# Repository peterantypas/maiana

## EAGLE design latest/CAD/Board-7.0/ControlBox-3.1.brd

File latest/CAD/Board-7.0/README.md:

# Board 7.0

This board is not yet completely validated, but its individual components are already proven.

Main improvements:

- The RX path features a MiniCircuits PSA4-5043+ LNA and a SAW filter from RFMI
- The DC/DC switch is now a synchronous buck with spread spectrum support for reduced EMI
- The 10000uF supercapacitor is back as an option in case transmission currents cause too much voltage drop at the input
- There are explicit signals to control status LEDs (GNSS, RX, TX)

There are two assembly variants, with and without the supercap. Firmware will support either without any special considerations, as it enforces a 5 second minimum interval between consecutive transmissions. This is more than enough to recharge a depleted supercap.

The control circuit is designed to fit inside a Hammond 1551KFLGY case (with appropriate cutouts). It features a single on/off button as well as a "TX on/off" slider switch. Control logic is implemented in a customized GreenPAK mixed signal IC (SLG46537V):

Using this type of IC avoids yet another microcontroller with firmware. The GreenPAK instruments latched overcurrent protection, debounces the on/off button, and acts as an LED driver. The design file for the IC (.gp5) is included. If you are an electronics enthusiast and you're not familiar with this family of ICs yet, I think it's time to change that ;)

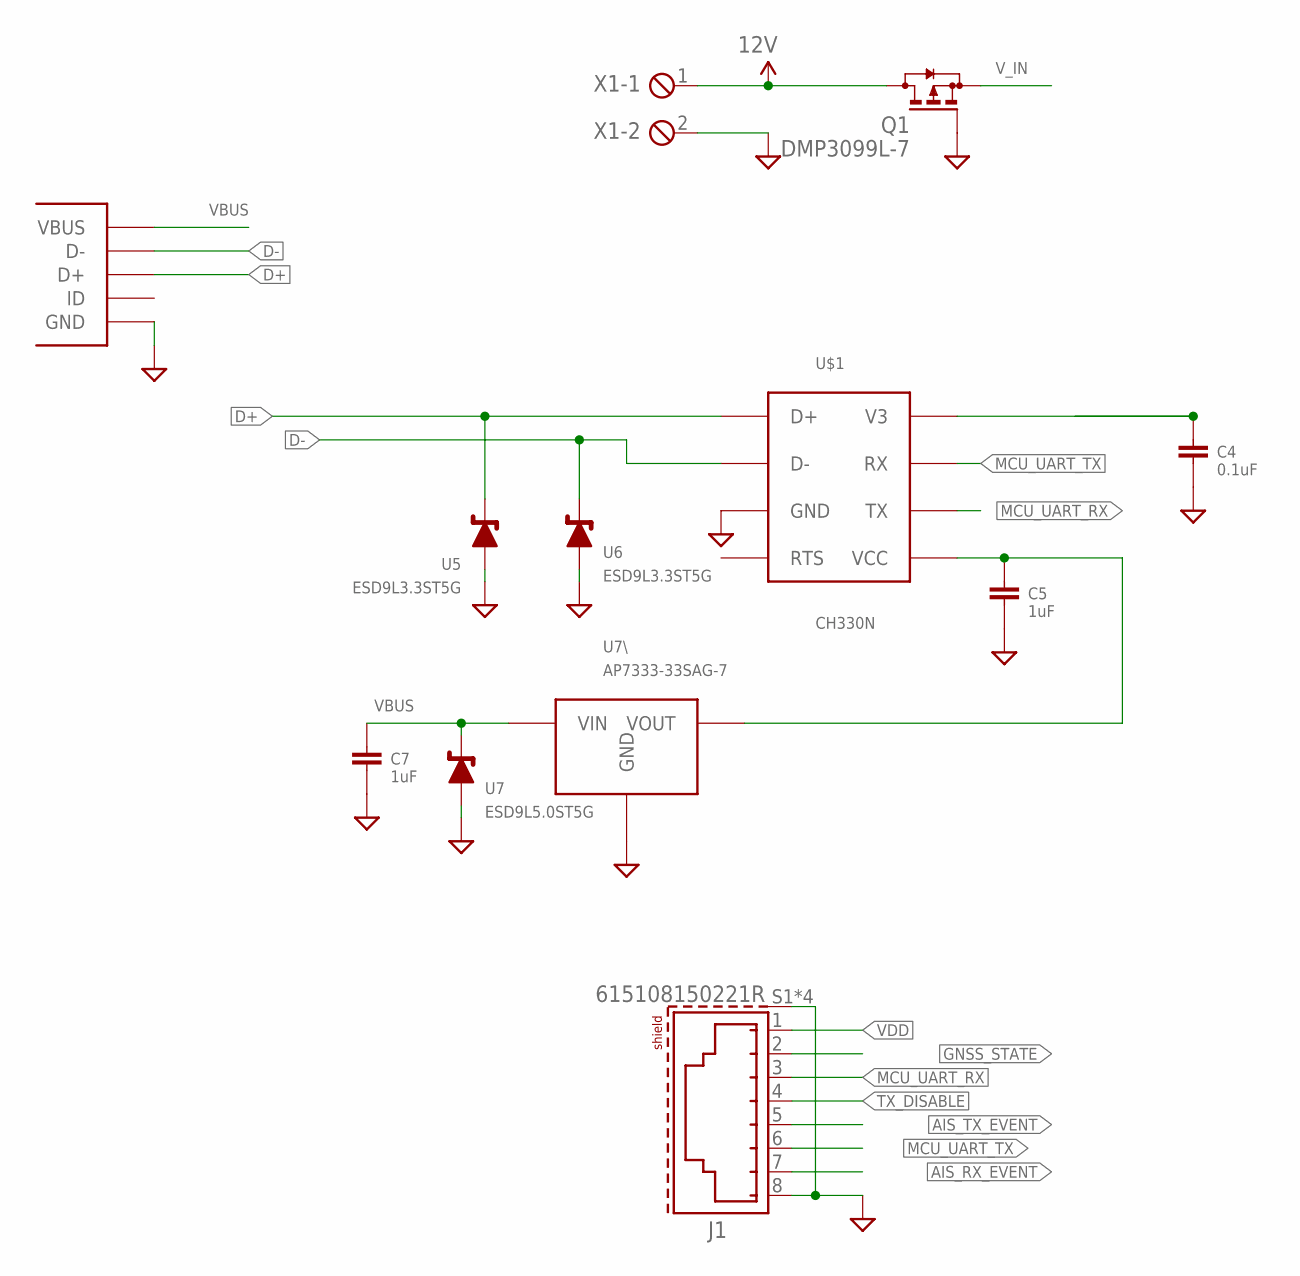
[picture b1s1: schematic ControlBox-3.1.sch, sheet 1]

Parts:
C4: 0.1uF; 0603
C5, C7: 1uF; 0603
J1: 615108150221R
Q1: DMP3099L-7; SOT23
U5, U6: ESD9L3.3ST5G; SODFL1006X40N
U7: ESD9L5.0ST5G; SODFL1006X40N
U7\: AP7333-33SAG-7; SOT-23
U$1: CH330N; SOIC-8
U$2: MICRO_USB
X1: MPT2; 2POL254

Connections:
12V: Q1.3 (D), X1.1
AIS_RX_EVENT: J1.7; also elsewhere on the board
AIS_TX_EVENT: J1.5; also elsewhere on the board
D+: U5.1, U$1.1 (D+), U$2.D+
D-: U6.1, U$1.2 (D-), U$2.D-
GND: C4.P$2 (2), C5.P$2 (2), C7.P$2 (2), J1.8, J1.S1 (SHIELD), J1.S2 (SHIELD), J1.S3 (SHIELD), J1.S4 (SHIELD), Q1.1 (G), U5.2, U6.2, U7.2, U7\.3 (GND), U$1.3 (GND), U$2.GND, U$2.MT1 (GND), U$2.MT2 (GND), U$2.P$1 (GND), U$2.P$2 (GND), X1.2; also elsewhere on the board
GNSS_STATE: J1.2; also elsewhere on the board
MCU_UART_RX: J1.3, U$1.6 (TX)
MCU_UART_TX: J1.6, U$1.7 (RX)
unnamed: C4.P$1 (1), U$1.8 (V3)
unnamed: C5.P$1 (1), U7\.2 (VOUT), U$1.5 (VCC)
TX_DISABLE: J1.4; also elsewhere on the board
VBUS: C7.P$1 (1), U7.1, U7\.1 (VIN), U$2.VBUS
VDD: J1.1; also elsewhere on the board
V_IN: Q1.2 (S); also elsewhere on the board

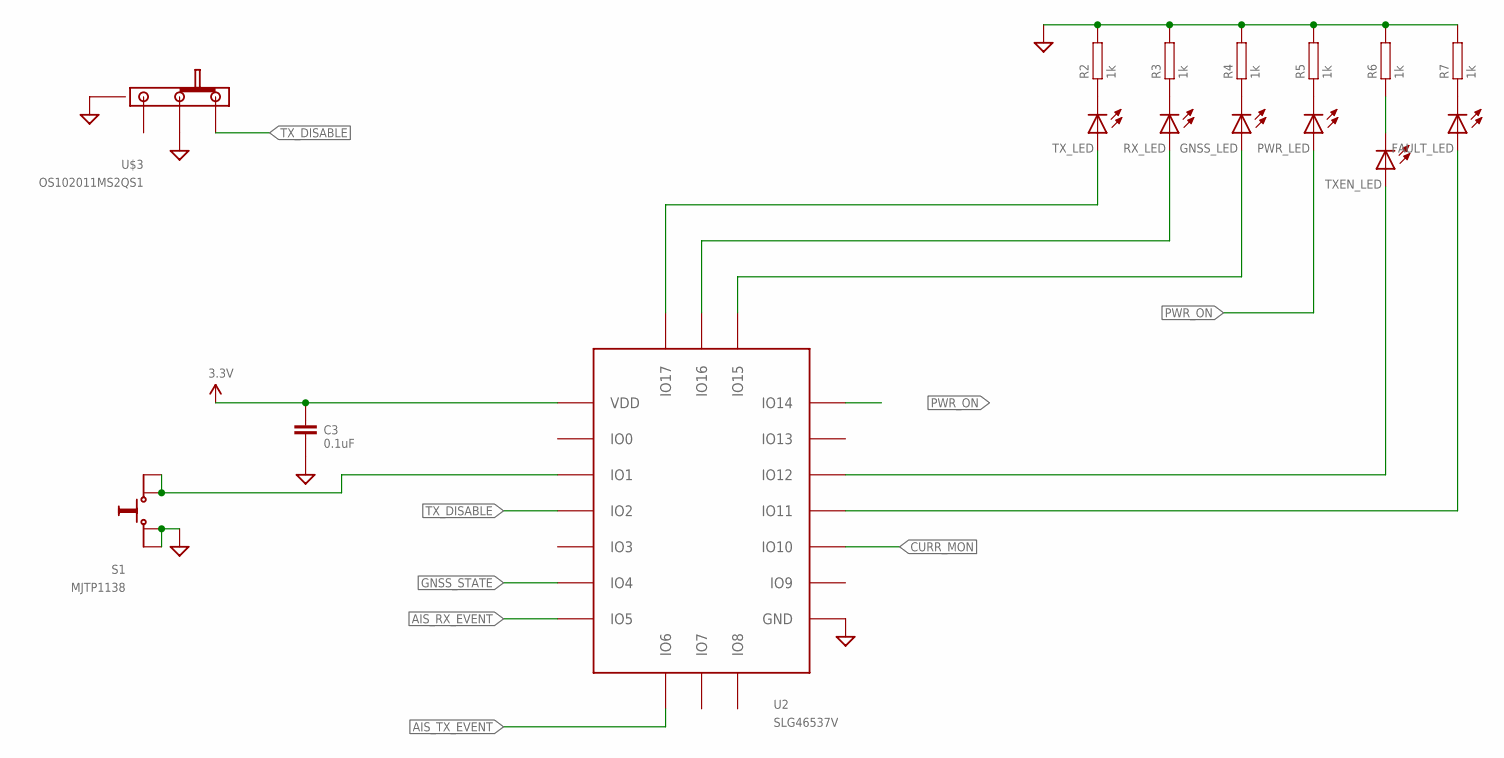
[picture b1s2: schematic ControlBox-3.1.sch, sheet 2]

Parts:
C3: 0.1uF; 0603
FAULT_LED: LEDCHIPLED_0603; CHIPLED_0603
GNSS_LED: LEDCHIPLED_0603; CHIPLED_0603
PWR_LED: LEDCHIPLED_0603; CHIPLED_0603
R2, R3, R4, R5, R6, R7: 1k; 0603
RX_LED: LEDCHIPLED_0603; CHIPLED_0603
S1: MJTP1138
TXEN_LED: LEDCHIPLED_0603; CHIPLED_0603
TX_LED: LEDCHIPLED_0603; CHIPLED_0603
U2: SLG46537V; STQFN20L
U$3: OS102011MS2QS1; SPDT-PTH

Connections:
3.3V: C3.P$1 (1), U2.P$1 (VDD); also elsewhere on the board
AIS_RX_EVENT: U2.P$7 (IO5); also elsewhere on the board
AIS_TX_EVENT: U2.P$8 (IO6); also elsewhere on the board
BTN: S1.P$1 (A), S1.P$4 (A), U2.P$3 (IO1)
CURR_MON: U2.P$13 (IO10); also elsewhere on the board
FAULT_LED: FAULT_LED.A, U2.P$14 (IO11)
GND: C3.P$2 (2), R2.P$2, R3.P$2, R4.P$2, R5.P$2, R6.P$2, R7.P$2, S1.P$2 (B), S1.P$3 (B), U2.P$11 (GND), U$3.P$2 (2), U$3.P$4 (SHLD), U$3.P$5 (SHLD); also elsewhere on the board
GNSS_LED: GNSS_LED.A, U2.P$18 (IO15)
GNSS_STATE: U2.P$6 (IO4); also elsewhere on the board
unnamed: R2.P$1, TX_LED.C
unnamed: R3.P$1, RX_LED.C
unnamed: GNSS_LED.C, R4.P$1
unnamed: PWR_LED.C, R5.P$1
unnamed: R6.P$1, TXEN_LED.C
unnamed: FAULT_LED.C, R7.P$1
PWR_ON: PWR_LED.A, U2.P$17 (IO14); also elsewhere on the board
RX_LED: RX_LED.A, U2.P$19 (IO16)
TX_DISABLE: U2.P$4 (IO2), U$3.P$1 (1); also elsewhere on the board
TX_EN_LED: TXEN_LED.A, U2.P$15 (IO12)
TX_LED: TX_LED.A, U2.P$20 (IO17)

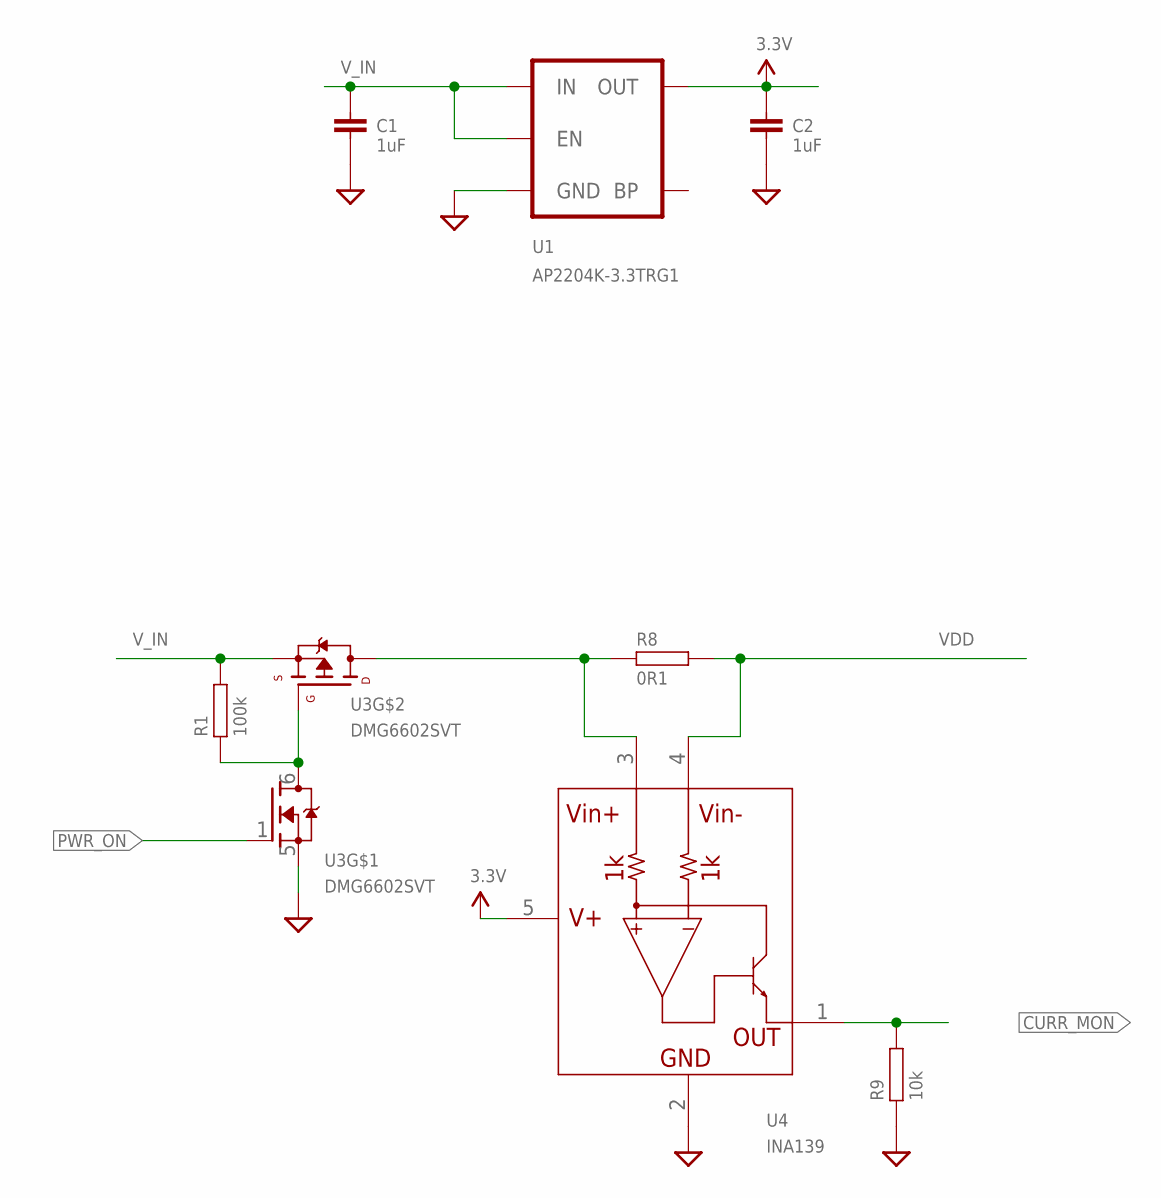
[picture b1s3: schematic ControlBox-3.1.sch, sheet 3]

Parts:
C1, C2: 1uF; 0603
R1: 100k; 0603
R8: 0R1; 1206
R9: 10k; 0603
U1: AP2204K-3.3TRG1; SOT23-5
U3: DMG6602SVT; SOT23-6
U4: INA139; SOT23-5

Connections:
3.3V: C2.P$1 (1), U1.5 (OUT), U4.5 (V+); also elsewhere on the board
CURR_MON: R9.P$2, U4.1 (OUT); also elsewhere on the board
GND: C1.P$2 (2), C2.P$2 (2), R9.P$1, U1.2 (GND), U3.5 (S), U4.2 (GND); also elsewhere on the board
unnamed: R1.P$1, U3.3 (G), U3.6 (D)
unnamed: R8.P$1, U3.4 (D), U4.3 (VIN+)
PWR_ON: U3.1 (G); also elsewhere on the board
VDD: R8.P$2, U4.4 (VIN-); also elsewhere on the board
V_IN: C1.P$1 (1), R1.P$2, U1.1 (IN), U1.3 (EN), U3.2 (S); also elsewhere on the board

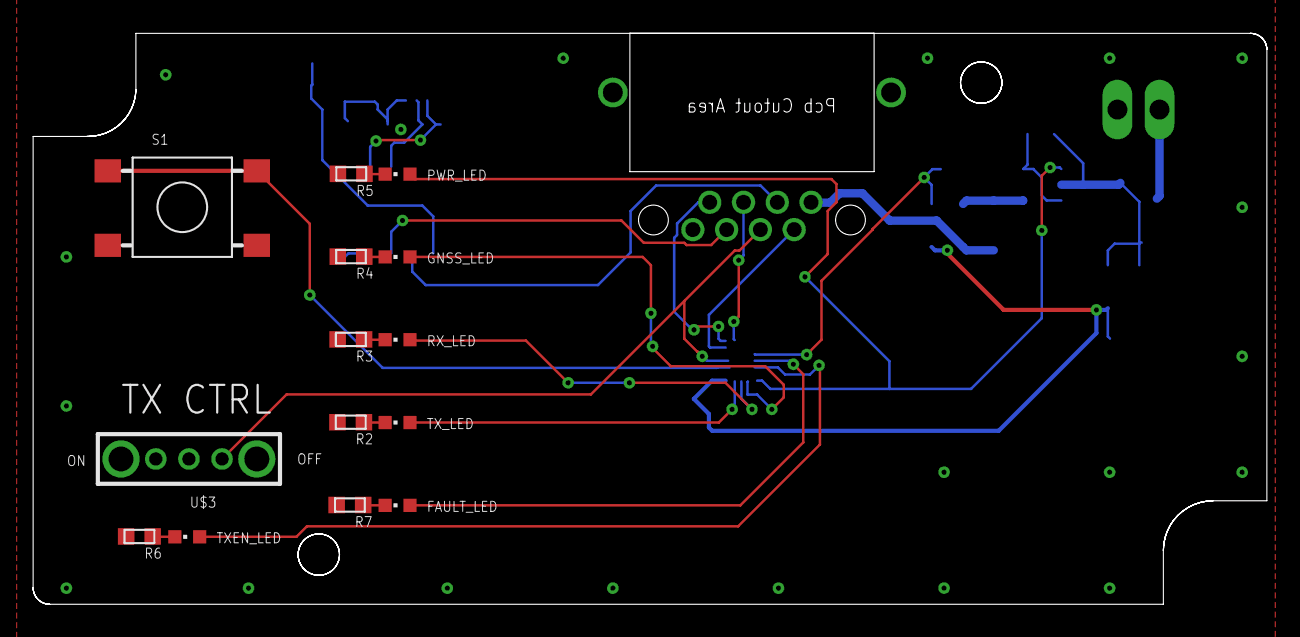
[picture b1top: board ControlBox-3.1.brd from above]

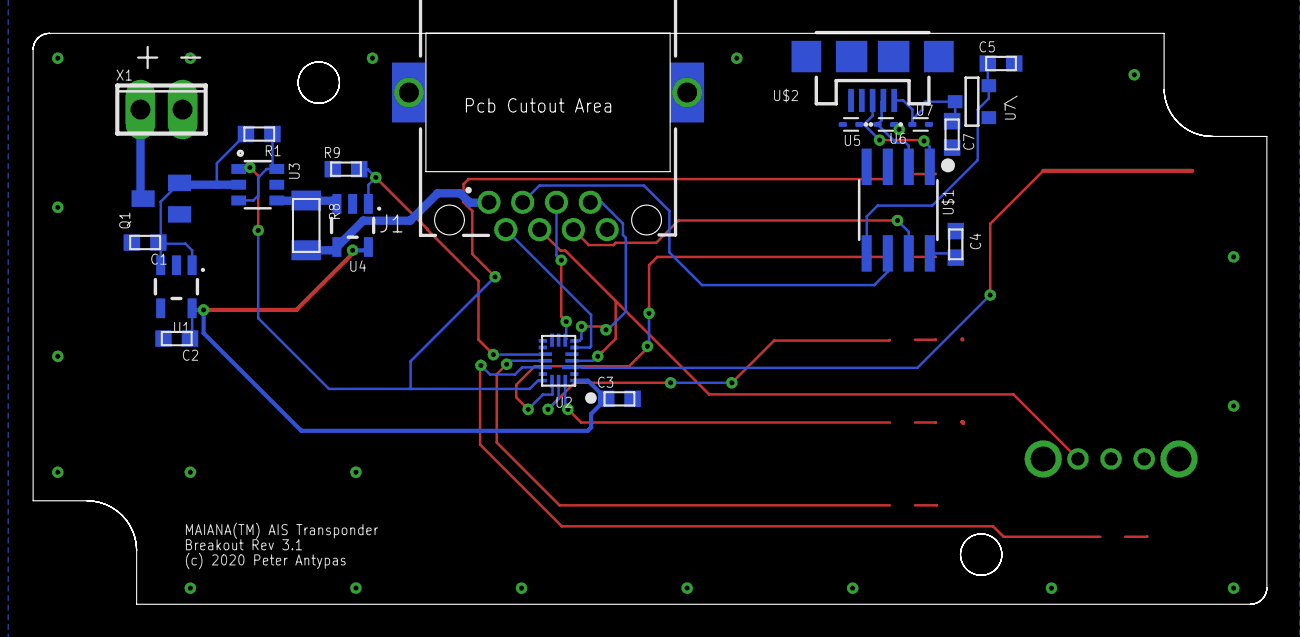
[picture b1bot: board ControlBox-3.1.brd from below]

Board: 2 copper layers, 74.5 x 34.5 mm, 36 parts (22 on the bottom side), 32 nets.

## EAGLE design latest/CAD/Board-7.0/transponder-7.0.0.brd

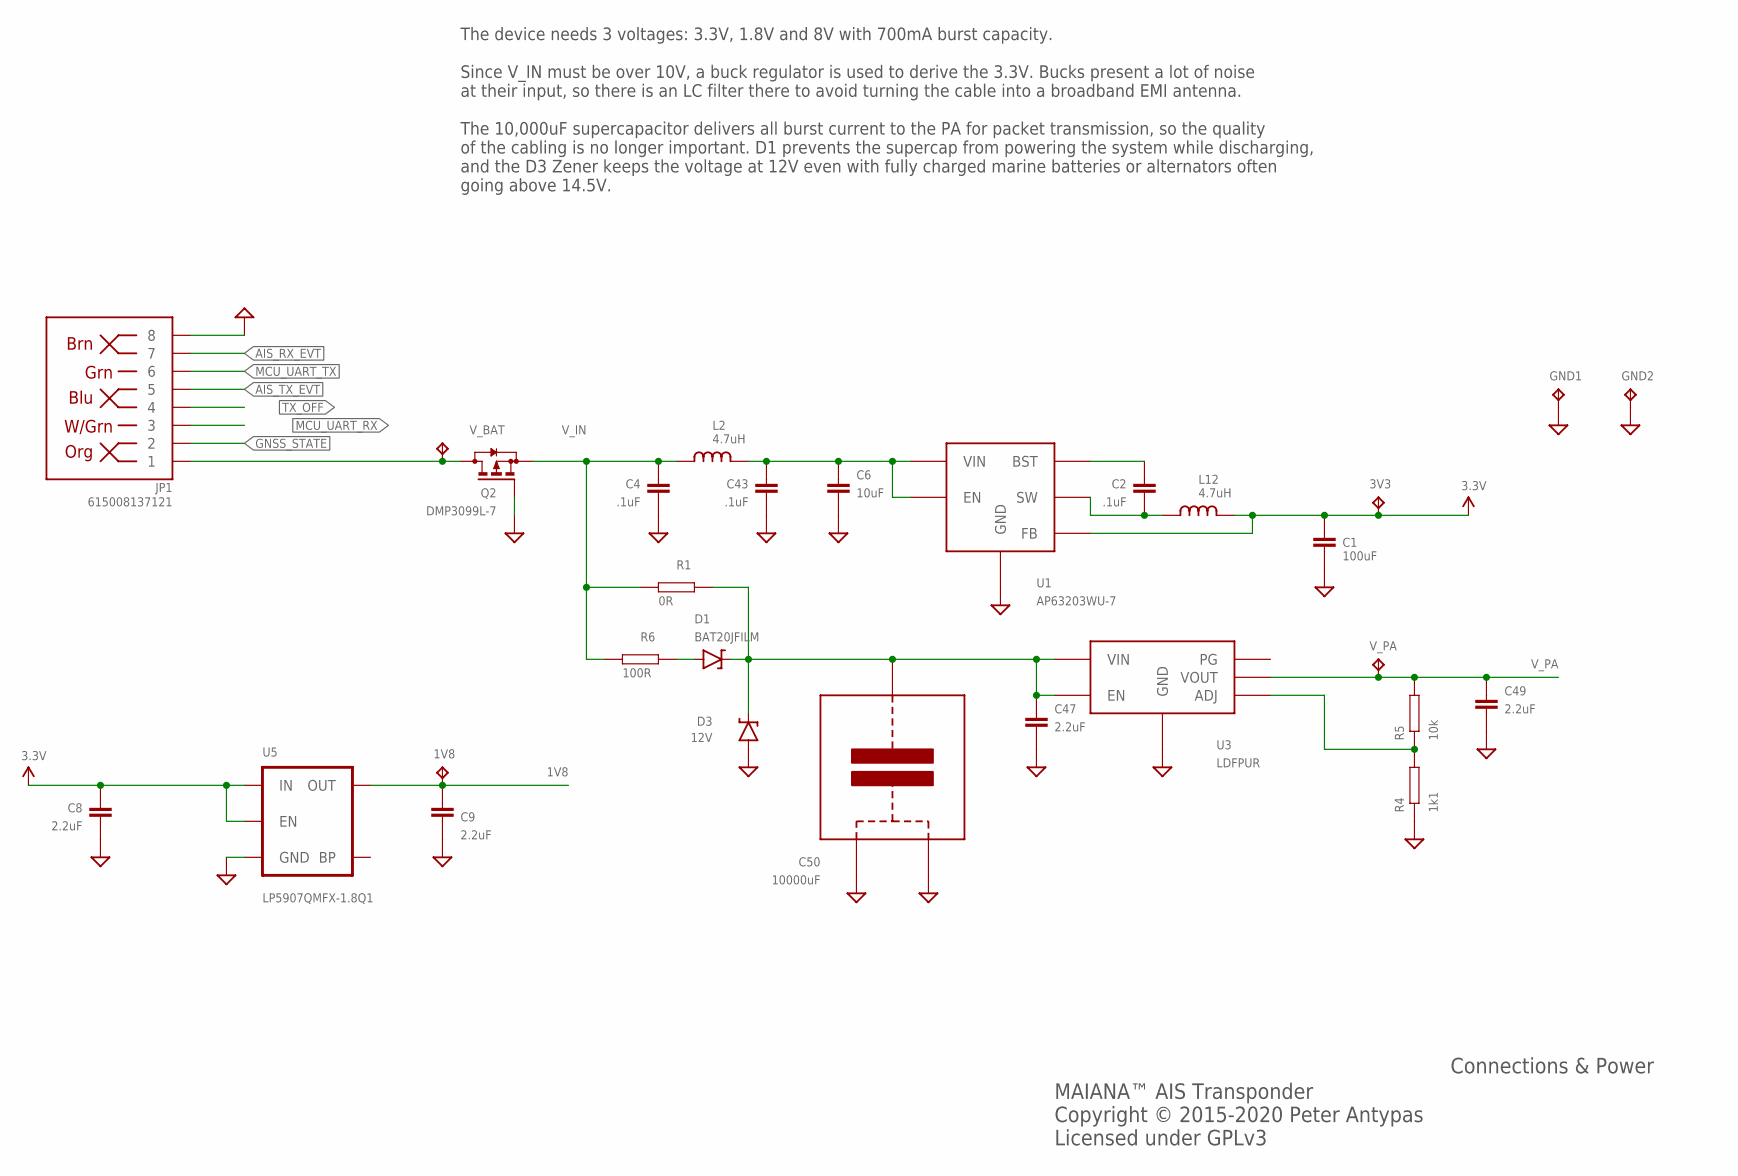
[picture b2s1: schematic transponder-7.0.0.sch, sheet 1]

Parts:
1V8, 3V3: TPTP12R; TP12R
C1: 100uF; 1206; PARTNO JMK316ABJ107ML-T
C2, C4, C43: .1uF; 0603; PARTNO EMK107B7104KAHT
C6: 10uF; 0805; PARTNO EMK212ABJ106KG-T
C8, C9, C47, C49: 2.2uF; 0603; PARTNO EMK107BJ225KA-T
C50: 10000uF; BZ05; PARTNO BZ05CA103ZSB
D1: BAT20JFILM; SOD323; PARTNO BAT20JFILM
D3: 12V; SOD-323; PARTNO MM3Z12VST1G
GND1, GND2: TPTP16R; TP16R
JP1: 615008137121; RJ45-8; PARTNO ‎615008137121‎
L2, L12: 4.7uH; 0805; PARTNO MLZ2012M4R7WT000
Q2: DMP3099L-7; SOT23; PARTNO DMP3099L-7
R1: 0R; 0603; PARTNO RC0603FR-070RL
R4: 1k1; 0603; PARTNO RC0603JR-071K1L
R5: 10k; 0603; PARTNO RC0603JR-0710KL
R6: 100R; 0603; PARTNO RC0603FR-07100RL
U1: AP63203WU-7; SOT23-6
U3: LDFPUR; DFN-6; PARTNO LDFPUR
U5: LP5907QMFX-1.8Q1; SOT23-5; PARTNO LP5907QMFX-1.8Q1
V_BAT: TPTP12R; TP12R
V_PA: TPTP12R; TP12R

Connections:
1V8: 1V8.TP, C9.P$1 (1), U5.5 (OUT); also elsewhere on the board
3.3V: 3V3.TP, C1.P$1 (1), C8.P$1 (1), L12.P$2 (2), U1.1 (FB), U5.1 (IN), U5.3 (EN); also elsewhere on the board
AIS_RX_EVT: JP1.7; also elsewhere on the board
AIS_TX_EVT: JP1.5; also elsewhere on the board
BST: C2.P$1 (1), U1.6 (BST)
GND: C1.P$2 (2), C4.P$2 (2), C6.P$2 (2), C8.P$2 (2), C9.P$2 (2), C43.P$2 (2), C47.P$2 (2), C49.P$2 (2), C50.P$1, C50.P$2, D3.A, GND1.TP, GND2.TP, JP1.8, Q2.1 (G), R4.P$1, U1.4 (GND), U3.P$4 (GND), U3.P$7 (GND), U5.2 (GND); also elsewhere on the board
GNSS_STATE: JP1.2; also elsewhere on the board
MCU_UART_RX: JP1.3; also elsewhere on the board
MCU_UART_TX: JP1.6; also elsewhere on the board
unnamed: D1.A, R6.P$2
unnamed: C6.P$1 (1), C43.P$1 (1), L2.P$2 (2), U1.2 (EN), U1.3 (VIN)
unnamed: R4.P$2, R5.P$1, U3.P$2 (ADJ)
SW: C2.P$2 (2), L12.P$1 (1), U1.5 (SW)
TX_OFF: JP1.4; also elsewhere on the board
V_BAT: JP1.1, Q2.3 (D), V_BAT.TP
V_IN: C4.P$1 (1), L2.P$1 (1), Q2.2 (S), R1.P$1, R6.P$1
V_PA: C49.P$1 (1), R5.P$2, U3.P$1 (VOUT), V_PA.TP; also elsewhere on the board
V_PA_SRC: C47.P$1 (1), C50.P$3, D1.C, D3.C, R1.P$2, U3.P$5 (EN), U3.P$6 (VIN)

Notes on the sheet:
Connections & Power
MAIANA™ AIS Transponder Copyright © 2015-2020 Peter Antypas Licensed under GPLv3
The device needs 3 voltages: 3.3V, 1.8V and 8V with 700mA burst capacity. Since V_IN must be over 10V, a buck regulator is used to derive the 3.3V. Bucks present a lot of noise at their input, so there is an LC filter there to avoid turning the cable into a broadband EMI antenna. The 10,000uF super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

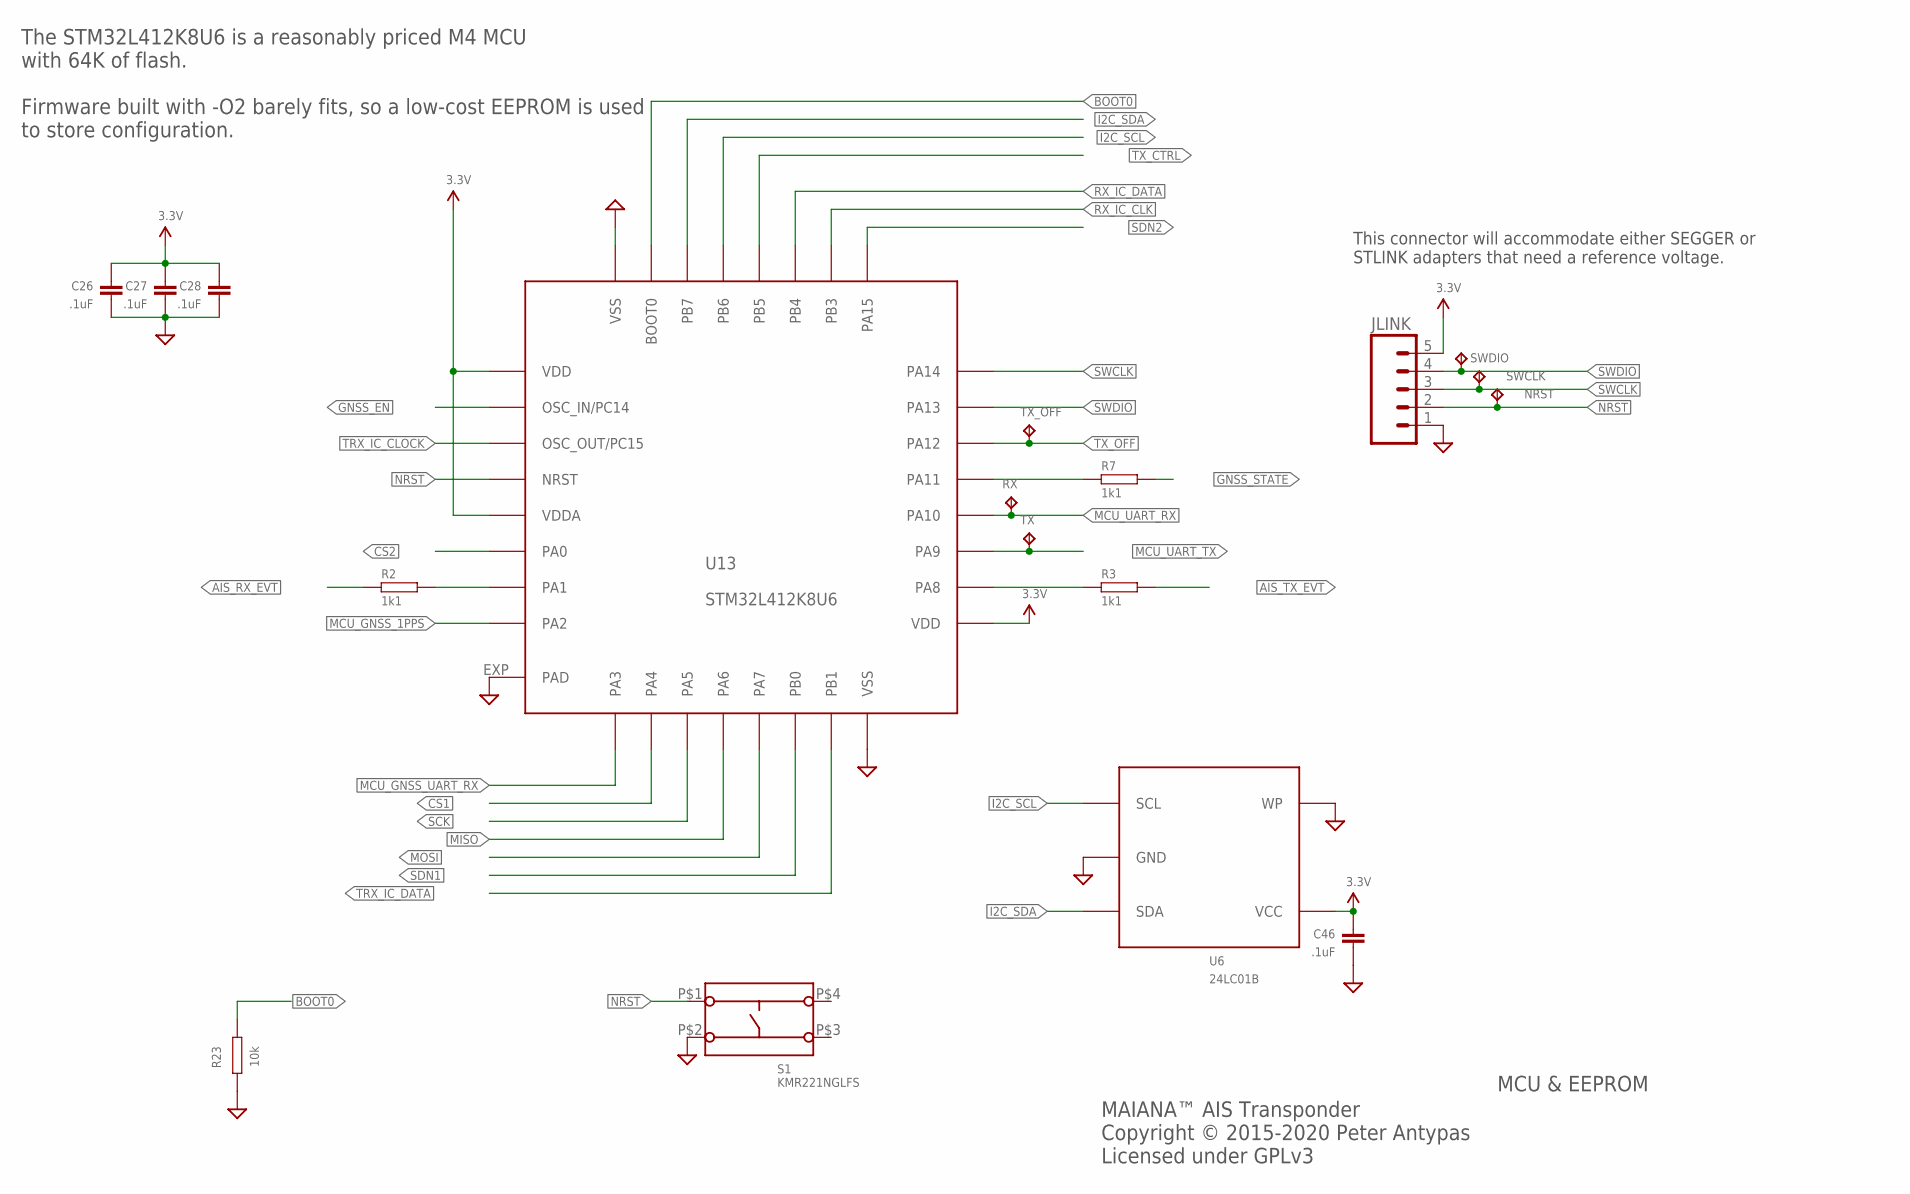
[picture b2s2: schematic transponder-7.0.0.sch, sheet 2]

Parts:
C26, C27, C28, C46: .1uF; 0603; PARTNO EMK107B7104KAHT
JLINK: M05PTH; 1X05
NRST: TPTP12R; TP12R
R2, R3, R7: 1k1; 0603; PARTNO RC0603JR-071K1L
R23: 10k; 0603; PARTNO RC0603JR-0710KL
RX: TPTP12R; TP12R
S1: KMR221NGLFS
SWCLK: TPTP12R; TP12R
SWDIO: TPTP12R; TP12R
TX: TPTP12R; TP12R
TX_OFF: TPTP12R; TP12R
U6: 24LC01B; SOT23-5; PARTNO 24LC01BT-I/OT
U13: STM32L412K8U6; QFN32; PARTNO STM32L412K8U6

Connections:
3.3V: C26.P$1 (1), C27.P$1 (1), C28.P$1 (1), C46.P$1 (1), JLINK.5, U6.4 (VCC), U13.1 (VDD), U13.5 (VDDA), U13.17 (VDD); also elsewhere on the board
AIS_RX_EVT: R2.P$1; also elsewhere on the board
AIS_TX_EVT: R3.P$2; also elsewhere on the board
BOOT0: R23.P$1, U13.31 (BOOT0)
CS1: U13.10 (PA4); also elsewhere on the board
CS2: U13.6 (PA0); also elsewhere on the board
GND: C26.P$2 (2), C27.P$2 (2), C28.P$2 (2), C46.P$2 (2), JLINK.1, R23.P$2, S1.P$2 (S2), U6.2 (GND), U6.5 (WP), U13.16 (VSS), U13.32 (VSS), U13.EXP (PAD); also elsewhere on the board
GNSS_EN: U13.2 (OSC_IN/PC14); also elsewhere on the board
GNSS_STATE: R7.P$2; also elsewhere on the board
I2C_SCL: U6.1 (SCL), U13.29 (PB6)
I2C_SDA: U6.3 (SDA), U13.30 (PB7)
MCU_GNSS_1PPS: U13.8 (PA2); also elsewhere on the board
MCU_GNSS_UART_RX: U13.9 (PA3); also elsewhere on the board
MCU_UART_RX: RX.TP, U13.20 (PA10); also elsewhere on the board
MCU_UART_TX: TX.TP, U13.19 (PA9); also elsewhere on the board
MISO: U13.12 (PA6); also elsewhere on the board
MOSI: U13.13 (PA7); also elsewhere on the board
unnamed: R2.P$2, U13.7 (PA1)
unnamed: R3.P$1, U13.18 (PA8)
unnamed: R7.P$1, U13.21 (PA11)
NRST: JLINK.2, NRST.TP, S1.P$1 (S1), U13.4 (NRST)
RX_IC_CLK: U13.26 (PB3); also elsewhere on the board
RX_IC_DATA: U13.27 (PB4); also elsewhere on the board
SCK: U13.11 (PA5); also elsewhere on the board
SDN1: U13.14 (PB0); also elsewhere on the board
SDN2: U13.25 (PA15); also elsewhere on the board
SWCLK: JLINK.3, SWCLK.TP, U13.24 (PA14)
SWDIO: JLINK.4, SWDIO.TP, U13.23 (PA13)
TRX_IC_CLOCK: U13.3 (OSC_OUT/PC15); also elsewhere on the board
TRX_IC_DATA: U13.15 (PB1); also elsewhere on the board
TX_CTRL: U13.28 (PB5); also elsewhere on the board
TX_OFF: TX_OFF.TP, U13.22 (PA12); also elsewhere on the board

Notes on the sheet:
MCU & EEPROM
MAIANA™ AIS Transponder Copyright © 2015-2020 Peter Antypas Licensed under GPLv3
The STM32L412K8U6 is a reasonably priced M4 MCU with 64K of flash. Firmware built with -O2 barely fits, so a low-cost EEPROM is used to store configuration.
This connector will accommodate either SEGGER or STLINK adapters that need a reference voltage.

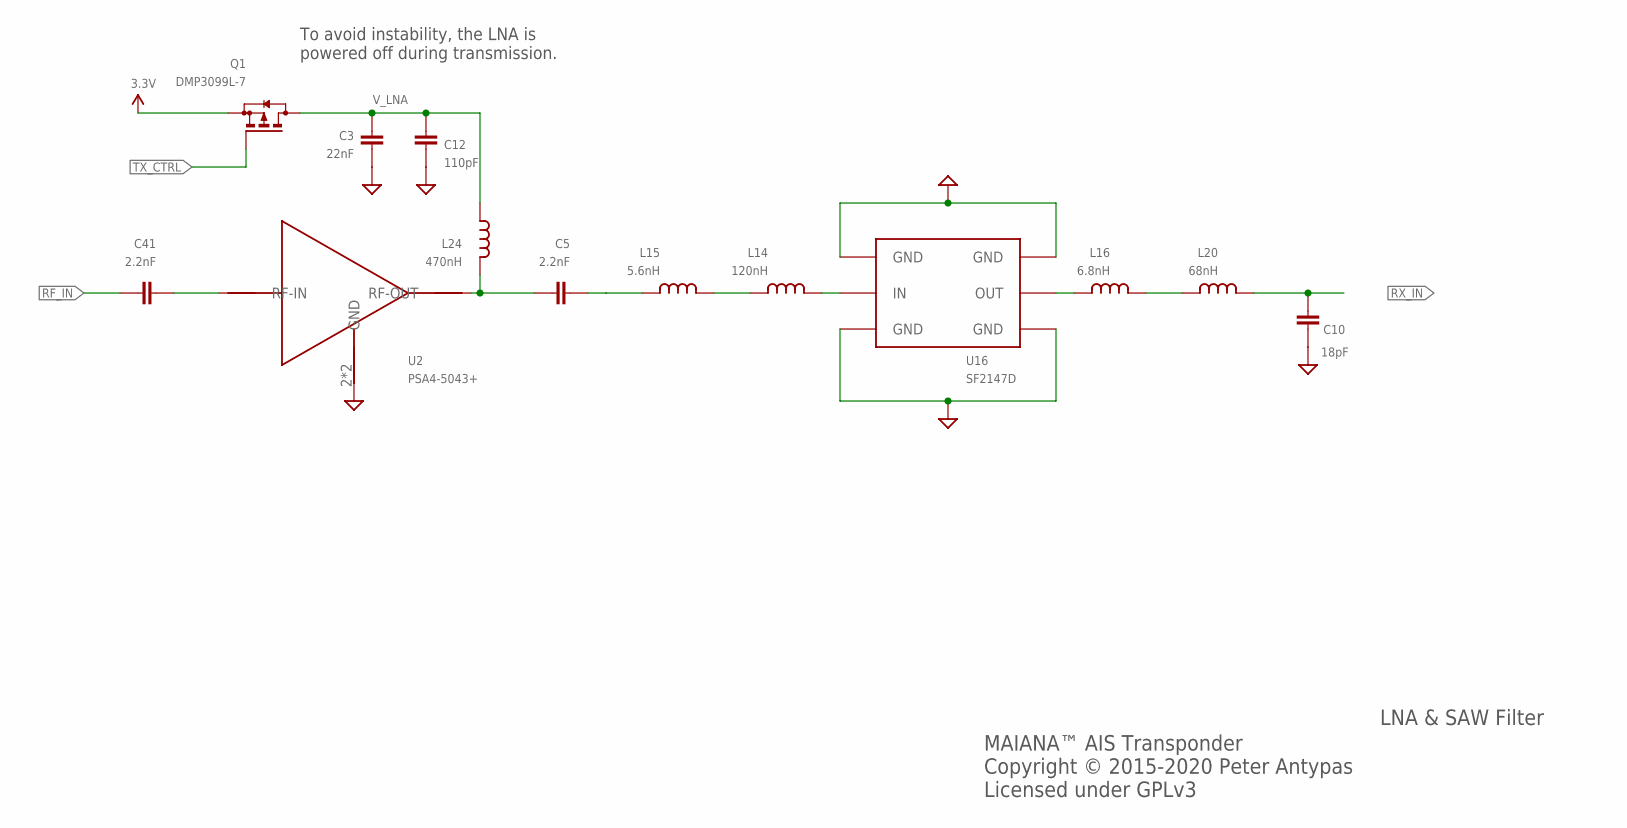
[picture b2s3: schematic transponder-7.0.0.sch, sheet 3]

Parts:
C3: 22nF; 0603; PARTNO GRM188R71E223KA01D
C5, C41: 2.2nF; 0603; PARTNO GRM1885C1H222JA01J
C10: 18pF; 0603; PARTNO 06035A180JAT4A
C12: 110pF; 0603; PARTNO GRM1885C2A111JA01D
L14: 120nH; 0603; PARTNO LQW18ASR12G0ZD
L15: 5.6nH; 0603; PARTNO LQW18AN5N6G8ZD
L16: 6.8nH; 0603; PARTNO LQW18AN6N8C10D
L20: 68nH; 0603; PARTNO LQW18AN68NG00D
L24: 470nH; 0603; PARTNO HK1608R47J-T
Q1: DMP3099L-7; SOT23; PARTNO DMP3099L-7
U2: PSA4-5043+
U16: SF2147D; SAW_FILTER1; PARTNO SF2147D

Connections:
3.3V: Q1.2 (S); also elsewhere on the board
GND: C3.P$2 (2), C10.P$1 (1), C12.P$1 (1), U2.2 (GND), U2.4 (GND), U16.P$1 (GND), U16.P$3 (GND), U16.P$4 (GND), U16.P$6 (GND); also elsewhere on the board
unnamed: L14.P$1 (1), U16.P$2 (IN)
unnamed: C41.P$2 (2), U2.3 (RF-IN)
unnamed: L14.P$2 (2), L15.P$1 (1)
unnamed: C5.P$1 (1), L24.P$2 (2), U2.1 (RF-OUT)
unnamed: C5.P$2 (2), L15.P$2 (2)
unnamed: L16.P$2 (2), U16.P$5 (OUT)
unnamed: L16.P$1 (1), L20.P$2 (2)
RF_IN: C41.P$1 (1); also elsewhere on the board
RX_IN: C10.P$2 (2), L20.P$1 (1); also elsewhere on the board
TX_CTRL: Q1.1 (G); also elsewhere on the board
V_LNA: C3.P$1 (1), C12.P$2 (2), L24.P$1 (1), Q1.3 (D)

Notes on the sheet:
LNA & SAW Filter
MAIANA™ AIS Transponder Copyright © 2015-2020 Peter Antypas Licensed under GPLv3
To avoid instability, the LNA is powered off during transmission.

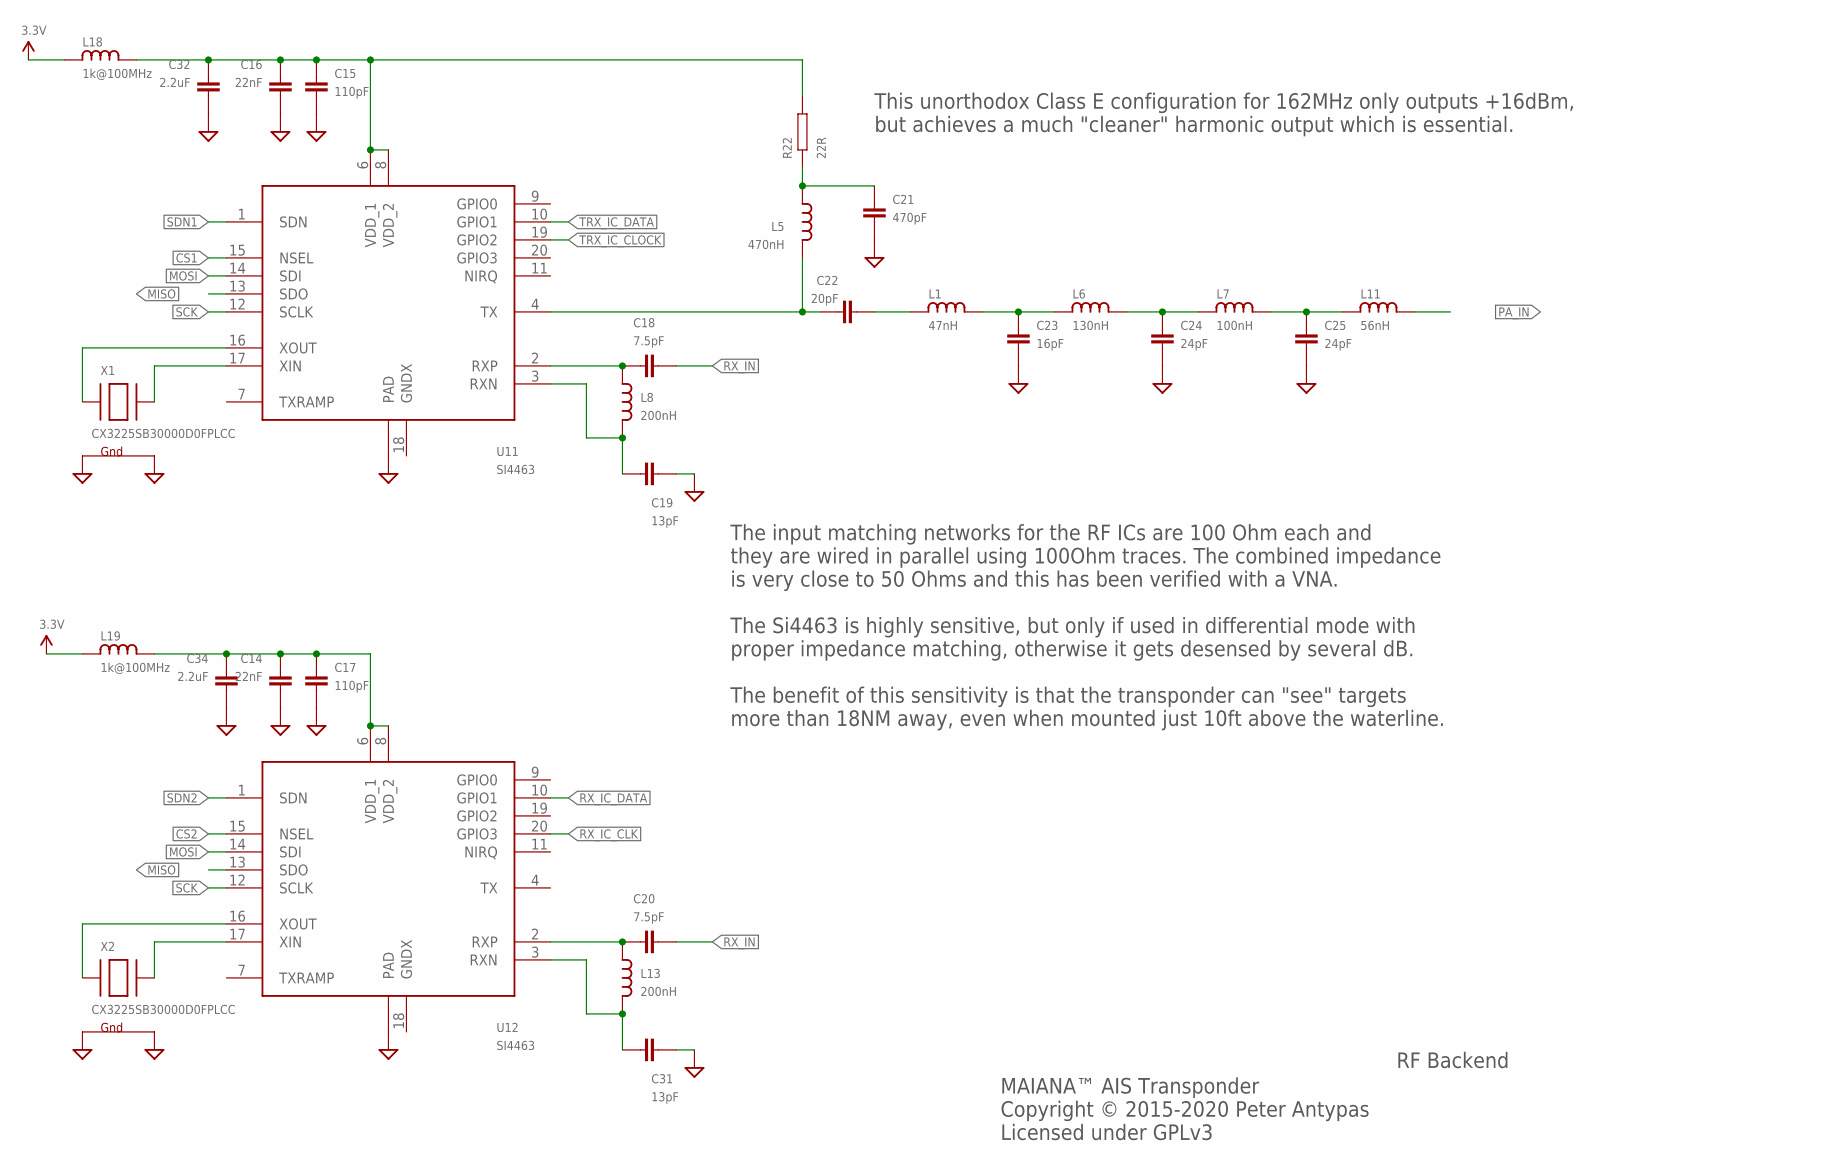
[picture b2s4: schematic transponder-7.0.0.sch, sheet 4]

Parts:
C14, C16: 22nF; 0603; PARTNO GRM188R71E223KA01D
C15, C17: 110pF; 0603; PARTNO GRM1885C2A111JA01D
C18, C20: 7.5pF; 0603; PARTNO GRM1885C1H7R5DA01D
C19, C31: 13pF; 0603; PARTNO GRM1885C1H130JA01D
C21: 470pF; 0603; PARTNO GRM1885C1H471JA01D
C22: 20pF; 0603; PARTNO GRM1885C1H200JA01D
C23: 16pF; 0603; PARTNO GCM1885C2A160JA16D
C24, C25: 24pF; 0603; PARTNO GRM1885C2A240JA01D
C32, C34: 2.2uF; 0603; PARTNO EMK107BJ225KA-T
L1: 47nH; 0603; PARTNO LQW18AN47NG00D
L5: 470nH; 0603; PARTNO HK1608R47J-T
L6: 130nH; 0603; PARTNO LQW18ANR13G00D
L7: 100nH; 0603; PARTNO LQW18ANR10G00D
L8, L13: 200nH; 0603; PARTNO LQW18ANR20J00D
L11: 56nH; 0603; PARTNO LQW18AN56NG00D
L18, L19: 1k@100MHz; 0603; PARTNO MPZ1608S102ATA00
R22: 22R; 0603; PARTNO RC0603JR-0722RL
U11, U12: SI4463; PARTNO SI4463-C2A-GMR
X1, X2: CX3225SB30000D0FPLCC; NX3225; PARTNO CX3225SB30000D0FPLCC

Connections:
3.3V: L18.P$1 (1), L19.P$1 (1); also elsewhere on the board
CS1: U11.15 (NSEL); also elsewhere on the board
CS2: U12.15 (NSEL); also elsewhere on the board
GND: C14.P$2 (2), C15.P$2 (2), C16.P$2 (2), C17.P$2 (2), C19.P$1 (1), C21.P$2 (2), C23.P$2 (2), C24.P$2 (2), C25.P$2 (2), C31.P$1 (1), C32.P$2 (2), C34.P$2 (2), U11.EXP (PAD), U12.EXP (PAD), X1.2 (G2), X1.4 (G1), X2.2 (G2), X2.4 (G1); also elsewhere on the board
MISO: U11.13 (SDO), U12.13 (SDO); also elsewhere on the board
MOSI: U11.14 (SDI), U12.14 (SDI); also elsewhere on the board
unnamed: C15.P$1 (1), C16.P$1 (1), C32.P$1 (1), L18.P$2 (2), R22.P$2, U11.6 (VDD_1), U11.8 (VDD_2)
unnamed: C19.P$2 (2), L8.P$2 (2), U11.3 (RXN)
unnamed: C18.P$1 (1), L8.P$1 (1), U11.2 (RXP)
unnamed: C24.P$1 (1), L6.P$2 (2), L7.P$1 (1)
unnamed: C25.P$1 (1), L7.P$2 (2), L11.P$1 (1)
unnamed: C23.P$1 (1), L1.P$2 (2), L6.P$1 (1)
unnamed: C14.P$1 (1), C17.P$1 (1), C34.P$1 (1), L19.P$2 (2), U12.6 (VDD_1), U12.8 (VDD_2)
unnamed: U12.16 (XOUT), X2.1 (X1)
unnamed: U12.17 (XIN), X2.3 (X2)
unnamed: U11.16 (XOUT), X1.1 (X1)
unnamed: U11.17 (XIN), X1.3 (X2)
unnamed: C20.P$1 (1), L13.P$1 (1), U12.2 (RXP)
unnamed: C31.P$2 (2), L13.P$2 (2), U12.3 (RXN)
unnamed: C22.P$1 (1), L5.P$2 (2), U11.4 (TX)
unnamed: C21.P$1 (1), L5.P$1 (1), R22.P$1
unnamed: C22.P$2 (2), L1.P$1 (1)
PA_IN: L11.P$2 (2); also elsewhere on the board
RX_IC_CLK: U12.20 (GPIO3); also elsewhere on the board
RX_IC_DATA: U12.10 (GPIO1); also elsewhere on the board
RX_IN: C18.P$2 (2), C20.P$2 (2); also elsewhere on the board
SCK: U11.12 (SCLK), U12.12 (SCLK); also elsewhere on the board
SDN1: U11.1 (SDN); also elsewhere on the board
SDN2: U12.1 (SDN); also elsewhere on the board
TRX_IC_CLOCK: U11.19 (GPIO2); also elsewhere on the board
TRX_IC_DATA: U11.10 (GPIO1); also elsewhere on the board

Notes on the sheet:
RF Backend
MAIANA™ AIS Transponder Copyright © 2015-2020 Peter Antypas Licensed under GPLv3
This unorthodox Class E configuration for 162MHz only outputs +16dBm, but achieves a much "cleaner" harmonic output which is essential.
The input matching networks for the RF ICs are 100 Ohm each and they are wired in parallel using 100Ohm traces. The combined impedance is very close to 50 Ohms and this has been verified with a VNA. The Si4463 is highly sensitive, but only if used in differential mode with proper impedance matching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

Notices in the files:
latest/CAD/Board-7.0/ControlBox-3.1.brd:
(c) 2020 Peter Antypas
latest/CAD/Board-9.3/rj45-breakout-9.3.brd:
(c)2020 P. Antypas
latest/CAD/NMEA0183Breakout/NMEA0183Breakout-2.0.brd:
(c)2021 P. Antypas
parts and their libraries:
SparkFun-PowerIC: Licensing: Creative Commons ShareAlike 4.0 International - https://creativecommons.org/licenses/by-sa/4.0
COPYRIGHT: Copyright (C) 2018 Accelerated Designs. All rights reserved
